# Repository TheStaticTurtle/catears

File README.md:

# Catears

High-tech, RGB LED-matrix cat ears, built for fun.

Each ear and each side of the headband carries a small 2D matrix of tiny XL-1010 WS2812B LEDs, driven by an ESP32-S3 running [WLED](https://kno.wled.ge/) with sound-reactive animations, all powered over a single USB-C cable.

## Revisions

| Version | Description |
|---------|-------------|
| V1 / V2 | The original 3D-printed ears and the single-color "Light-Up" variant from the C3CAT assembly (not mine, just the inspiration). |
| V3 | Full-band 5mm addressable COB RGB strip, custom 3D-printed frame, TinyPICO ESP32 and battery in a bulky box. |
| V4.1 | Ear-shaped LED matrix test board to validate the LEDs, power and WLED. |
| V4.2 | ESP32-S3 on the PCB, USB-PD and a buck converter per panel. Over-engineered: it overheated and WiFi was poor (2-layer, then 4-layer respin, then a bypassed DC-DC for 39C3). |
| V4.3 | Current version. Plain 5V in, MPM3805 for 3.3V, tuned WiFi antenna, grid-aligned LEDs, SLS-printed PA12 frame, silicone-mounted PCBs. |

## Repository layout

- `cad/`: 3D models of the headband and ears
- `electronics/`: KiCad projects for each PCB revision
- `wled/`: WLED config, presets and the 2D LED map (generated from the KiCad netlist by `gen_ledmap.py`)

## Read more

The full story, with the mistakes, photos and lessons learned, is in the article:
**[Building high-tech catears for fun and definitively not profit](https://blog.thestaticturtle.fr/building-high-tech-catears-for-fun-and-definitely-not-profit)**

## License

See [LICENSE.md](LICENSE.md).

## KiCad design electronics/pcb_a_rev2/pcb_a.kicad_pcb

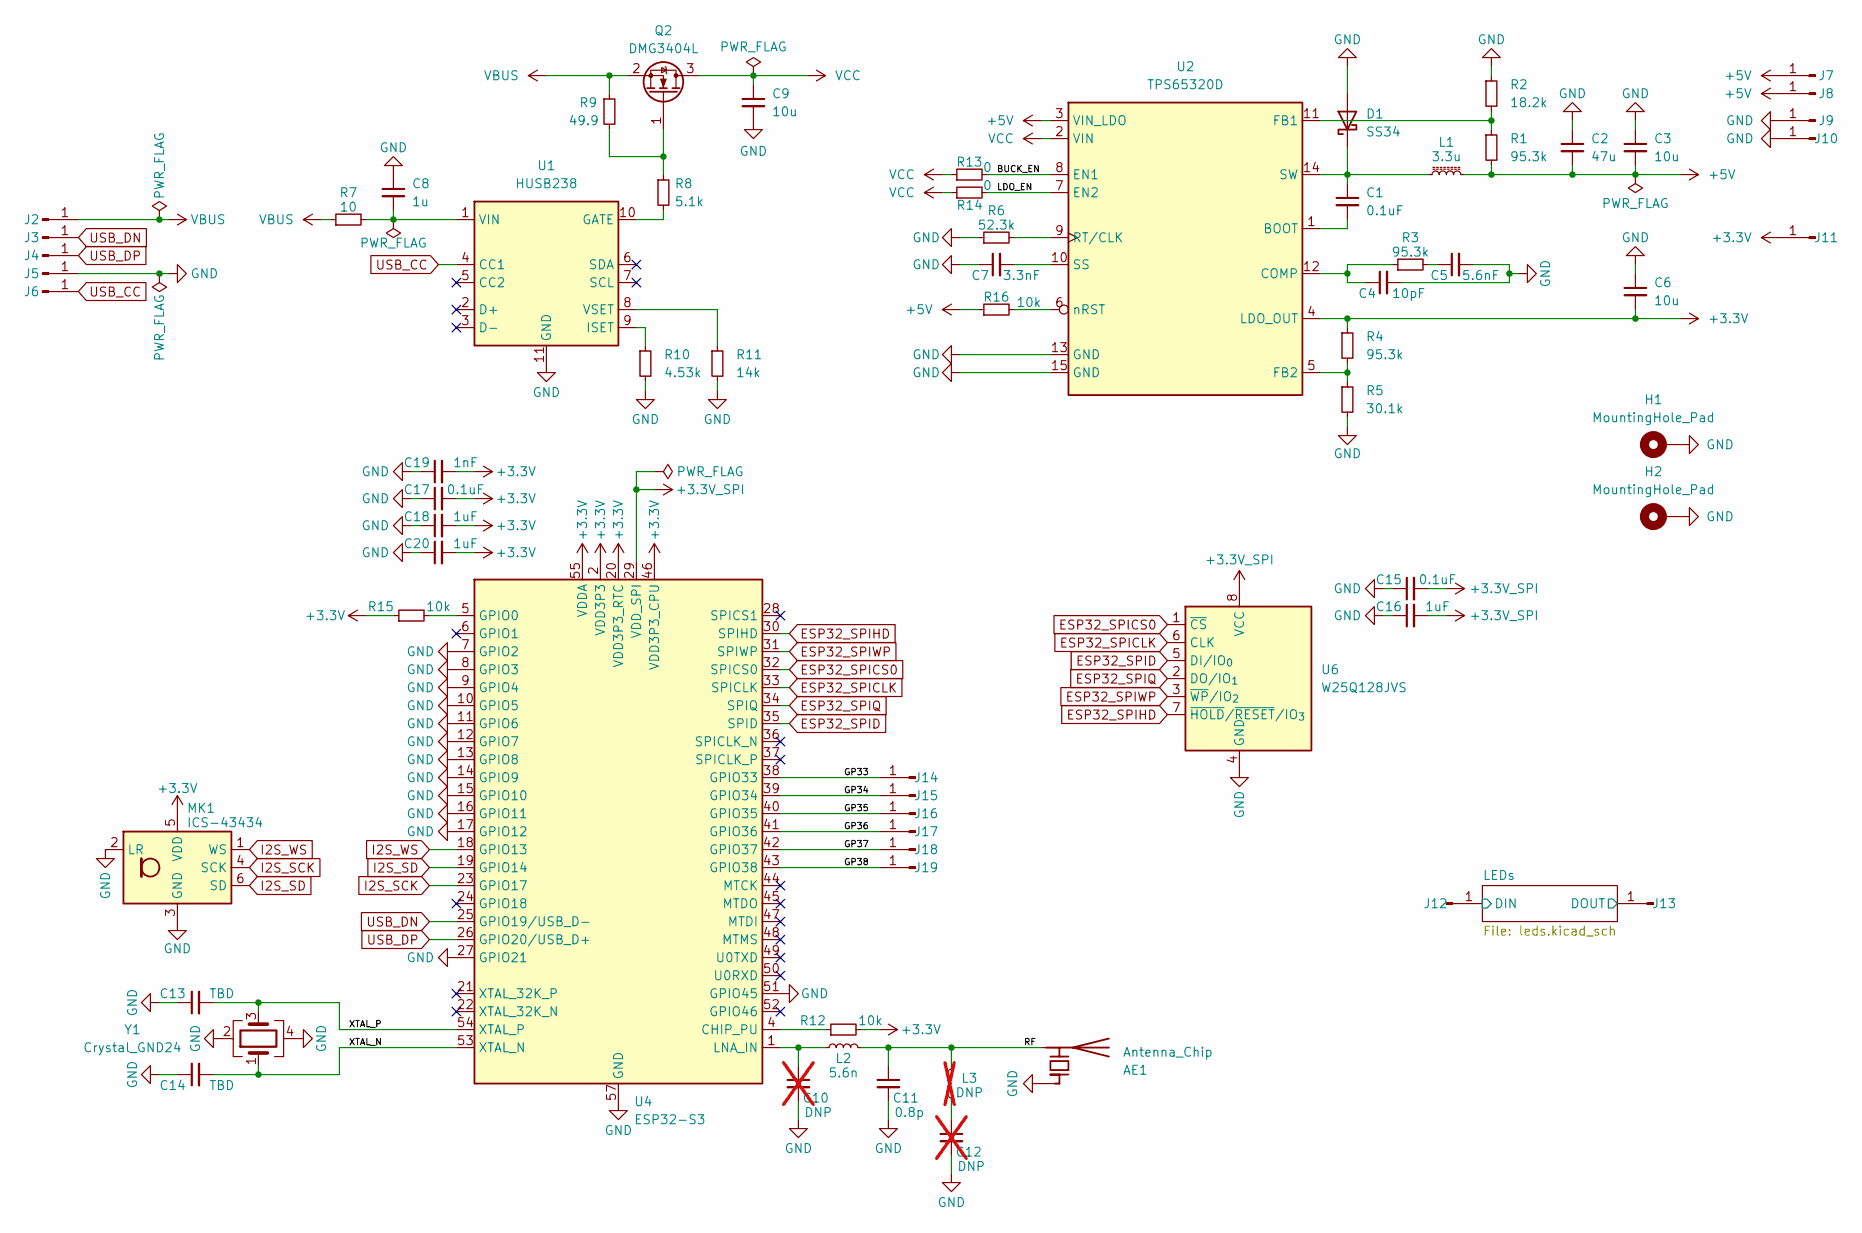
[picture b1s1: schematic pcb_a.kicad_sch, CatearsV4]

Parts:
AE1: Antenna_Chip; Johanson_2450AT43F0100
C1, C15, C17: 0.1uF; C_0603_1608Metric
C2: 47u; C_0603_1608Metric
C3, C6, C9: 10u; C_0603_1608Metric
C4: 10pF; C_0603_1608Metric
C5: 5.6nF; C_0603_1608Metric
C7: 3.3nF; C_0603_1608Metric
C8: 1u; C_0603_1608Metric
C10, C12: DNP; C_0603_1608Metric; not fitted
C11: 0.8p; C_0603_1608Metric
C13, C14: TBD; C_0603_1608Metric
C16, C18, C20: 1uF; C_0603_1608Metric
C19: 1nF; C_0603_1608Metric
D1: SS34; D_SMA
H1: MountingHole_Pad; 7466302R_thin
H2: MountingHole_Pad; 7466302R_thin_halved
J2, J3, J4, J5, J6, J7, J8, J9, J10, J11, J12, J13, J14, J15, J16, J17, J18, J19: Conn_01x01_Pin; TestPoint_Pad_1.5x1.5mm
L1: 3.3u; L_Wurth_WE-LQSH-4020
L2: 5.6n; L_0603_1608Metric
L3: DNP; L_0603_1608Metric; not fitted
MK1: ICS-43434; InvenSense_ICS-43434-6_3.5x2.65mm
Q2: DMG3404L; SOT-23
R1, R3, R4: 95.3k; R_0603_1608Metric
R2: 18.2k; R_0603_1608Metric
R5: 30.1k; R_0603_1608Metric
R6: 52.3k; R_0603_1608Metric
R7: 10; R_0603_1608Metric
R8: 5.1k; R_0603_1608Metric
R9: 49.9; R_0603_1608Metric
R10: 4.53k; R_0603_1608Metric
R11: 14k; R_0603_1608Metric
R12, R15, R16: 10k; R_0603_1608Metric
R13, R14: 0; R_0603_1608Metric
U1: HUSB238; DFN-10-1EP_3x3mm_P0.5mm_EP1.58x2.35mm
U2: TPS65320D; HTSSOP-14-1EP_4.4x5mm_P0.65mm_EP3.4x5mm_Mask3x3.1mm
U4: ESP32-S3; QFN-56-1EP_7x7mm_P0.4mm_EP4x4mm
U6: W25Q128JVS; SOIC-8_5.3x5.3mm_P1.27mm
Y1: Crystal_GND24; Crystal_SMD_5032-4Pin_5.0x3.2mm

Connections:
+3.3V: C6.2, C17.2, C18.2, C19.2, C20.2, J11.1, MK1.5 (VDD), R4.1, R12.2, R15.1, U2.4 (LDO_OUT), U4.2 (VDD3P3), U4.3 (VDD3P3), U4.20 (VDD3P3_RTC), U4.46 (VDD3P3_CPU), U4.55 (VDDA), U4.56 (VDDA)
+3.3V_SPI: C15.2, C16.2, U4.29 (VDD_SPI), U6.8 (VCC)
+5V: C2.2, C3.2, J7.1, J8.1, L1.2, R1.2, R16.1, U2.3 (VIN_LDO); also elsewhere on the board
/BUCK_EN: R13.2, U2.8 (EN1)
/GP33: J14.1, U4.38 (GPIO33)
/GP34: J15.1, U4.39 (GPIO34)
/GP35: J16.1, U4.40 (GPIO35)
/GP36: J17.1, U4.41 (GPIO36)
/GP37: J18.1, U4.42 (GPIO37)
/GP38: J19.1, U4.43 (GPIO38)
/LDO_EN: R14.2, U2.7 (EN2)
/LEDs/DIN: J12.1; also elsewhere on the board
/LEDs/DOUT: J13.1; also elsewhere on the board
/RF: AE1.2 (PCB_Trace), C11.1, L2.2, L3.2
/XTAL_N: C14.2, U4.53 (XTAL_N), Y1.1
/XTAL_P: C13.2, U4.54 (XTAL_P), Y1.3
ESP32_SPICLK: U4.33 (SPICLK), U6.6 (CLK)
ESP32_SPICS0: U4.32 (SPICS0), U6.1 (~CS)
ESP32_SPID: U4.35 (SPID), U6.5 (DI/IO_{0})
ESP32_SPIHD: U4.30 (SPIHD), U6.7 (~HOLD/~RESET/IO_{3})
ESP32_SPIQ: U4.34 (SPIQ), U6.2 (DO/IO_{1})
ESP32_SPIWP: U4.31 (SPIWP), U6.3 (~WP/IO_{2})
GND: AE1.1 (FEED), C2.1, C3.1, C4.2, C5.2, C6.1, C7.1, C8.1, C9.2, C10.2, C11.2, C12.2, C13.1, C14.1, C15.1, C16.1, C17.1, C18.1, C19.1, C20.1, D1.2 (A), H1.1, H2.1, J5.1, J9.1, J10.1, MK1.2 (LR), MK1.3 (GND), R2.1, R5.2, R6.1, R10.2, R11.2, U1.11 (GND), U2.13 (GND), U2.15 (GND), U4.7 (GPIO2), U4.8 (GPIO3), U4.9 (GPIO4), U4.10 (GPIO5), U4.11 (GPIO6), U4.12 (GPIO7), U4.13 (GPIO8), U4.14 (GPIO9), U4.15 (GPIO10), U4.16 (GPIO11), U4.17 (GPIO12), U4.27 (GPIO21), U4.51 (GPIO45), U4.57 (GND), U6.4 (GND), Y1.2, Y1.4; also elsewhere on the board
I2S_SCK: MK1.4 (SCK), U4.23 (GPIO17)
I2S_SD: MK1.6 (SD), U4.19 (GPIO14)
I2S_WS: MK1.1 (WS), U4.18 (GPIO13)
unnamed: C5.1, R3.2
unnamed: C12.1, L3.1
unnamed: C1.1, D1.1 (K), L1.1, U2.14 (SW)
unnamed: Q2.1 (G), R8.1, R9.2
unnamed: R8.2, U1.10 (GATE)
unnamed: R10.1, U1.9 (ISET)
unnamed: C8.2, R7.2, U1.1 (VIN)
unnamed: R11.1, U1.8 (VSET)
unnamed: C1.2, U2.1 (BOOT)
unnamed: C4.1, R3.1, U2.12 (COMP)
unnamed: R1.1, R2.2, U2.11 (FB1)
unnamed: R4.2, R5.1, U2.5 (FB2)
unnamed: R6.2, U2.9 (RT/CLK)
unnamed: C7.2, U2.10 (SS)
unnamed: R16.2, U2.6 (nRST)
unnamed: R12.1, U4.4 (CHIP_PU)
unnamed: R15.2, U4.5 (GPIO0)
unnamed: C10.1, L2.1, U4.1 (LNA_IN)
USB_CC: J6.1, U1.4 (CC1)
USB_DN: J3.1, U4.25 (GPIO19/USB_D-)
USB_DP: J4.1, U4.26 (GPIO20/USB_D+)
VBUS: J2.1, Q2.2 (S), R7.1, R9.1
VCC: C9.1, Q2.3 (D), R13.1, R14.1, U2.2 (VIN)

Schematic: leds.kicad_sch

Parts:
D2, D3, D4, D5, D6, D7, D8, D9, D10, D11, D12, D13, D14, D15, D16, D17, D18, D19, D20, D21, D22, D23, D24, D25, D26, D27, D28, D29, D30, D31, D32, D33, D34, D35, D36, D37, D38, D39, D40, D41, D42, D43, D44, D45, D46, D47, D48, D49, D50, D51, D52, D53, D54, D55, D56, D57, D58, D59, D60, D61, D62, D63, D64, D65, D66, D67, D68, D69, D70, D71, D72, D73, D74, D75, D76, D77, D78, D79, D80, D81, D82, D83, D84, D85, D86, D87, D88, D89, D90, D91, D92, D93, D94, D95, D96, D97, D98, D99, D100, D101, D102, D103, D104, D105, D106, D107, D108, D109, D110, D111, D112, D113, D114, D115, D116, D117, D118, D119, D120, D121, D122, D123, D124, D125, D126, D127, D128, D129, D130, D131, D132, D133, D134, D135, D136, D137, D138, D139, D140, D141, D142, D143, D144, D145, D146, D147, D148, D149, D150, D151, D152, D153, D154, D155, D156, D157, D158, D159, D160, D161, D162, D163, D164, D165, D166, D167, D168, D169, D170, D171, D172, D173, D174, D175, D176, D177, D178, D179, D180, D181, D182, D183, D184, D185, D186, D187, D188, D189, D190, D191, D192, D193, D194, D195, D196, D197, D198, D199, D200, D201, D202, D203, D204, D205, D206, D207, D208, D209, D210, D211, D212, D213, D214, D215, D216, D217, D218, D219, D220, D221, D222, D223, D224, D225, D226, D227, D228, D229, D230, D231, D232, D233, D234, D235, D236, D237, D238, D239, D240, D241, D242, D243, D244, D245, D246, D247, D248, D249, D250, D251, D252, D253, D254, D255, D257, D258, D259, D260, D261, D262, D263, D264, D265, D266, D267, D268, D269, D270, D271, D272, D273, D274, D275, D276, D277, D278, D279, D280, D281, D282, D283, D284, D285, D286, D287, D288, D289, D290, D291, D292, D293, D294, D295, D296, D297, D298, D299, D300, D301, D302, D303, D304, D305, D306, D307, D308, D309, D310, D311, D312, D313, D314, D315, D316, D317, D318, D319, D320, D321, D322, D323, D324, D325, D326, D327, D328: XL-1010; XL-1010RGBC

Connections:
+5V: D2.2 (VDD), D3.2 (VDD), D4.2 (VDD), D5.2 (VDD), D6.2 (VDD), D7.2 (VDD), D8.2 (VDD), D9.2 (VDD), D10.2 (VDD), D11.2 (VDD), D12.2 (VDD), D13.2 (VDD), D14.2 (VDD), D15.2 (VDD), D16.2 (VDD), D17.2 (VDD), D18.2 (VDD), D19.2 (VDD), D20.2 (VDD), D21.2 (VDD), D22.2 (VDD), D23.2 (VDD), D24.2 (VDD), D25.2 (VDD), D26.2 (VDD), D27.2 (VDD), D28.2 (VDD), D29.2 (VDD), D30.2 (VDD), D31.2 (VDD), D32.2 (VDD), D33.2 (VDD), D34.2 (VDD), D35.2 (VDD), D36.2 (VDD), D37.2 (VDD), D38.2 (VDD), D39.2 (VDD), D40.2 (VDD), D41.2 (VDD), D42.2 (VDD), D43.2 (VDD), D44.2 (VDD), D45.2 (VDD), D46.2 (VDD), D47.2 (VDD), D48.2 (VDD), D49.2 (VDD), D50.2 (VDD), D51.2 (VDD), D52.2 (VDD), D53.2 (VDD), D54.2 (VDD), D55.2 (VDD), D56.2 (VDD), D57.2 (VDD), D58.2 (VDD), D59.2 (VDD), D60.2 (VDD), D61.2 (VDD), D62.2 (VDD), D63.2 (VDD), D64.2 (VDD), D65.2 (VDD), D66.2 (VDD), D67.2 (VDD), D68.2 (VDD), D69.2 (VDD), D70.2 (VDD), D71.2 (VDD), D72.2 (VDD), D73.2 (VDD), D74.2 (VDD), D75.2 (VDD), D76.2 (VDD), D77.2 (VDD), D78.2 (VDD), D79.2 (VDD), D80.2 (VDD), D81.2 (VDD), D82.2 (VDD), D83.2 (VDD), D84.2 (VDD), D85.2 (VDD), D86.2 (VDD), D87.2 (VDD), D88.2 (VDD), D89.2 (VDD), D90.2 (VDD), D91.2 (VDD), D92.2 (VDD), D93.2 (VDD), D94.2 (VDD), D95.2 (VDD), D96.2 (VDD), D97.2 (VDD), D98.2 (VDD), D99.2 (VDD), D100.2 (VDD), D101.2 (VDD), D102.2 (VDD), D103.2 (VDD), D104.2 (VDD), D105.2 (VDD), D106.2 (VDD), D107.2 (VDD), D108.2 (VDD), D109.2 (VDD), D110.2 (VDD), D111.2 (VDD), D112.2 (VDD), D113.2 (VDD), D114.2 (VDD), D115.2 (VDD), D116.2 (VDD), D117.2 (VDD), D118.2 (VDD), D119.2 (VDD), D120.2 (VDD), D121.2 (VDD), D122.2 (VDD), D123.2 (VDD), D124.2 (VDD), D125.2 (VDD), D126.2 (VDD), D127.2 (VDD), D128.2 (VDD), D129.2 (VDD), D130.2 (VDD), D131.2 (VDD), D132.2 (VDD), D133.2 (VDD), D134.2 (VDD), D135.2 (VDD), D136.2 (VDD), D137.2 (VDD), D138.2 (VDD), D139.2 (VDD), D140.2 (VDD), D141.2 (VDD), D142.2 (VDD), D143.2 (VDD), D144.2 (VDD), D145.2 (VDD), D146.2 (VDD), D147.2 (VDD), D148.2 (VDD), D149.2 (VDD), D150.2 (VDD), D151.2 (VDD), D152.2 (VDD), D153.2 (VDD), D154.2 (VDD), D155.2 (VDD), D156.2 (VDD), D157.2 (VDD), D158.2 (VDD), D159.2 (VDD), D160.2 (VDD), D161.2 (VDD), D162.2 (VDD), D163.2 (VDD), D164.2 (VDD), D165.2 (VDD), D166.2 (VDD), D167.2 (VDD), D168.2 (VDD), D169.2 (VDD), D170.2 (VDD), D171.2 (VDD), D172.2 (VDD), D173.2 (VDD), D174.2 (VDD), D175.2 (VDD), D176.2 (VDD), D177.2 (VDD), D178.2 (VDD), D179.2 (VDD), D180.2 (VDD), D181.2 (VDD), D182.2 (VDD), D183.2 (VDD), D184.2 (VDD), D185.2 (VDD), D186.2 (VDD), D187.2 (VDD), D188.2 (VDD), D189.2 (VDD), D190.2 (VDD), D191.2 (VDD), D192.2 (VDD), D193.2 (VDD), D194.2 (VDD), D195.2 (VDD), D196.2 (VDD), D197.2 (VDD), D198.2 (VDD), D199.2 (VDD), D200.2 (VDD), D201.2 (VDD), D202.2 (VDD), D203.2 (VDD), D204.2 (VDD), D205.2 (VDD), D206.2 (VDD), D207.2 (VDD), D208.2 (VDD), D209.2 (VDD), D210.2 (VDD), D211.2 (VDD), D212.2 (VDD), D213.2 (VDD), D214.2 (VDD), D215.2 (VDD), D216.2 (VDD), D217.2 (VDD), D218.2 (VDD), D219.2 (VDD), D220.2 (VDD), D221.2 (VDD), D222.2 (VDD), D223.2 (VDD), D224.2 (VDD), D225.2 (VDD), D226.2 (VDD), D227.2 (VDD), D228.2 (VDD), D229.2 (VDD), D230.2 (VDD), D231.2 (VDD), D232.2 (VDD), D233.2 (VDD), D234.2 (VDD), D235.2 (VDD), D236.2 (VDD), D237.2 (VDD), D238.2 (VDD), D239.2 (VDD), D240.2 (VDD), D241.2 (VDD), D242.2 (VDD), D243.2 (VDD), D244.2 (VDD), D245.2 (VDD), D246.2 (VDD), D247.2 (VDD), D248.2 (VDD), D249.2 (VDD), D250.2 (VDD), D251.2 (VDD), D252.2 (VDD), D253.2 (VDD), D254.2 (VDD), D255.2 (VDD), D257.2 (VDD), D258.2 (VDD), D259.2 (VDD), D260.2 (VDD), D261.2 (VDD), D262.2 (VDD), D263.2 (VDD), D264.2 (VDD), D265.2 (VDD), D266.2 (VDD), D267.2 (VDD), D268.2 (VDD), D269.2 (VDD), D270.2 (VDD), D271.2 (VDD), D272.2 (VDD), D273.2 (VDD), D274.2 (VDD), D275.2 (VDD), D276.2 (VDD), D277.2 (VDD), D278.2 (VDD), D279.2 (VDD), D280.2 (VDD), D281.2 (VDD), D282.2 (VDD), D283.2 (VDD), D284.2 (VDD), D285.2 (VDD), D286.2 (VDD), D287.2 (VDD), D288.2 (VDD), D289.2 (VDD), D290.2 (VDD), D291.2 (VDD), D292.2 (VDD), D293.2 (VDD), D294.2 (VDD), D295.2 (VDD), D296.2 (VDD), D297.2 (VDD), D298.2 (VDD), D299.2 (VDD), D300.2 (VDD), D301.2 (VDD), D302.2 (VDD), D303.2 (VDD), D304.2 (VDD), D305.2 (VDD), D306.2 (VDD), D307.2 (VDD), D308.2 (VDD), D309.2 (VDD), D310.2 (VDD), D311.2 (VDD), D312.2 (VDD), D313.2 (VDD), D314.2 (VDD), D315.2 (VDD), D316.2 (VDD), D317.2 (VDD), D318.2 (VDD), D319.2 (VDD), D320.2 (VDD), D321.2 (VDD), D322.2 (VDD), D323.2 (VDD), D324.2 (VDD), D325.2 (VDD), D326.2 (VDD), D327.2 (VDD), D328.2 (VDD); also elsewhere on the board
/LEDs/DIN: D2.4 (DIN); also elsewhere on the board
/LEDs/DOUT: D328.1 (DOUT); also elsewhere on the board
GND: D2.3 (VSS), D3.3 (VSS), D4.3 (VSS), D5.3 (VSS), D6.3 (VSS), D7.3 (VSS), D8.3 (VSS), D9.3 (VSS), D10.3 (VSS), D11.3 (VSS), D12.3 (VSS), D13.3 (VSS), D14.3 (VSS), D15.3 (VSS), D16.3 (VSS), D17.3 (VSS), D18.3 (VSS), D19.3 (VSS), D20.3 (VSS), D21.3 (VSS), D22.3 (VSS), D23.3 (VSS), D24.3 (VSS), D25.3 (VSS), D26.3 (VSS), D27.3 (VSS), D28.3 (VSS), D29.3 (VSS), D30.3 (VSS), D31.3 (VSS), D32.3 (VSS), D33.3 (VSS), D34.3 (VSS), D35.3 (VSS), D36.3 (VSS), D37.3 (VSS), D38.3 (VSS), D39.3 (VSS), D40.3 (VSS), D41.3 (VSS), D42.3 (VSS), D43.3 (VSS), D44.3 (VSS), D45.3 (VSS), D46.3 (VSS), D47.3 (VSS), D48.3 (VSS), D49.3 (VSS), D50.3 (VSS), D51.3 (VSS), D52.3 (VSS), D53.3 (VSS), D54.3 (VSS), D55.3 (VSS), D56.3 (VSS), D57.3 (VSS), D58.3 (VSS), D59.3 (VSS), D60.3 (VSS), D61.3 (VSS), D62.3 (VSS), D63.3 (VSS), D64.3 (VSS), D65.3 (VSS), D66.3 (VSS), D67.3 (VSS), D68.3 (VSS), D69.3 (VSS), D70.3 (VSS), D71.3 (VSS), D72.3 (VSS), D73.3 (VSS), D74.3 (VSS), D75.3 (VSS), D76.3 (VSS), D77.3 (VSS), D78.3 (VSS), D79.3 (VSS), D80.3 (VSS), D81.3 (VSS), D82.3 (VSS), D83.3 (VSS), D84.3 (VSS), D85.3 (VSS), D86.3 (VSS), D87.3 (VSS), D88.3 (VSS), D89.3 (VSS), D90.3 (VSS), D91.3 (VSS), D92.3 (VSS), D93.3 (VSS), D94.3 (VSS), D95.3 (VSS), D96.3 (VSS), D97.3 (VSS), D98.3 (VSS), D99.3 (VSS), D100.3 (VSS), D101.3 (VSS), D102.3 (VSS), D103.3 (VSS), D104.3 (VSS), D105.3 (VSS), D106.3 (VSS), D107.3 (VSS), D108.3 (VSS), D109.3 (VSS), D110.3 (VSS), D111.3 (VSS), D112.3 (VSS), D113.3 (VSS), D114.3 (VSS), D115.3 (VSS), D116.3 (VSS), D117.3 (VSS), D118.3 (VSS), D119.3 (VSS), D120.3 (VSS), D121.3 (VSS), D122.3 (VSS), D123.3 (VSS), D124.3 (VSS), D125.3 (VSS), D126.3 (VSS), D127.3 (VSS), D128.3 (VSS), D129.3 (VSS), D130.3 (VSS), D131.3 (VSS), D132.3 (VSS), D133.3 (VSS), D134.3 (VSS), D135.3 (VSS), D136.3 (VSS), D137.3 (VSS), D138.3 (VSS), D139.3 (VSS), D140.3 (VSS), D141.3 (VSS), D142.3 (VSS), D143.3 (VSS), D144.3 (VSS), D145.3 (VSS), D146.3 (VSS), D147.3 (VSS), D148.3 (VSS), D149.3 (VSS), D150.3 (VSS), D151.3 (VSS), D152.3 (VSS), D153.3 (VSS), D154.3 (VSS), D155.3 (VSS), D156.3 (VSS), D157.3 (VSS), D158.3 (VSS), D159.3 (VSS), D160.3 (VSS), D161.3 (VSS), D162.3 (VSS), D163.3 (VSS), D164.3 (VSS), D165.3 (VSS), D166.3 (VSS), D167.3 (VSS), D168.3 (VSS), D169.3 (VSS), D170.3 (VSS), D171.3 (VSS), D172.3 (VSS), D173.3 (VSS), D174.3 (VSS), D175.3 (VSS), D176.3 (VSS), D177.3 (VSS), D178.3 (VSS), D179.3 (VSS), D180.3 (VSS), D181.3 (VSS), D182.3 (VSS), D183.3 (VSS), D184.3 (VSS), D185.3 (VSS), D186.3 (VSS), D187.3 (VSS), D188.3 (VSS), D189.3 (VSS), D190.3 (VSS), D191.3 (VSS), D192.3 (VSS), D193.3 (VSS), D194.3 (VSS), D195.3 (VSS), D196.3 (VSS), D197.3 (VSS), D198.3 (VSS), D199.3 (VSS), D200.3 (VSS), D201.3 (VSS), D202.3 (VSS), D203.3 (VSS), D204.3 (VSS), D205.3 (VSS), D206.3 (VSS), D207.3 (VSS), D208.3 (VSS), D209.3 (VSS), D210.3 (VSS), D211.3 (VSS), D212.3 (VSS), D213.3 (VSS), D214.3 (VSS), D215.3 (VSS), D216.3 (VSS), D217.3 (VSS), D218.3 (VSS), D219.3 (VSS), D220.3 (VSS), D221.3 (VSS), D222.3 (VSS), D223.3 (VSS), D224.3 (VSS), D225.3 (VSS), D226.3 (VSS), D227.3 (VSS), D228.3 (VSS), D229.3 (VSS), D230.3 (VSS), D231.3 (VSS), D232.3 (VSS), D233.3 (VSS), D234.3 (VSS), D235.3 (VSS), D236.3 (VSS), D237.3 (VSS), D238.3 (VSS), D239.3 (VSS), D240.3 (VSS), D241.3 (VSS), D242.3 (VSS), D243.3 (VSS), D244.3 (VSS), D245.3 (VSS), D246.3 (VSS), D247.3 (VSS), D248.3 (VSS), D249.3 (VSS), D250.3 (VSS), D251.3 (VSS), D252.3 (VSS), D253.3 (VSS), D254.3 (VSS), D255.3 (VSS), D257.3 (VSS), D258.3 (VSS), D259.3 (VSS), D260.3 (VSS), D261.3 (VSS), D262.3 (VSS), D263.3 (VSS), D264.3 (VSS), D265.3 (VSS), D266.3 (VSS), D267.3 (VSS), D268.3 (VSS), D269.3 (VSS), D270.3 (VSS), D271.3 (VSS), D272.3 (VSS), D273.3 (VSS), D274.3 (VSS), D275.3 (VSS), D276.3 (VSS), D277.3 (VSS), D278.3 (VSS), D279.3 (VSS), D280.3 (VSS), D281.3 (VSS), D282.3 (VSS), D283.3 (VSS), D284.3 (VSS), D285.3 (VSS), D286.3 (VSS), D287.3 (VSS), D288.3 (VSS), D289.3 (VSS), D290.3 (VSS), D291.3 (VSS), D292.3 (VSS), D293.3 (VSS), D294.3 (VSS), D295.3 (VSS), D296.3 (VSS), D297.3 (VSS), D298.3 (VSS), D299.3 (VSS), D300.3 (VSS), D301.3 (VSS), D302.3 (VSS), D303.3 (VSS), D304.3 (VSS), D305.3 (VSS), D306.3 (VSS), D307.3 (VSS), D308.3 (VSS), D309.3 (VSS), D310.3 (VSS), D311.3 (VSS), D312.3 (VSS), D313.3 (VSS), D314.3 (VSS), D315.3 (VSS), D316.3 (VSS), D317.3 (VSS), D318.3 (VSS), D319.3 (VSS), D320.3 (VSS), D321.3 (VSS), D322.3 (VSS), D323.3 (VSS), D324.3 (VSS), D325.3 (VSS), D326.3 (VSS), D327.3 (VSS), D328.3 (VSS); also elsewhere on the board
unnamed: D2.1 (DOUT), D3.4 (DIN)
unnamed: D3.1 (DOUT), D4.4 (DIN)
unnamed: D4.1 (DOUT), D5.4 (DIN)
unnamed: D5.1 (DOUT), D6.4 (DIN)
unnamed: D6.1 (DOUT), D7.4 (DIN)
unnamed: D7.1 (DOUT), D8.4 (DIN)
unnamed: D8.1 (DOUT), D9.4 (DIN)
unnamed: D9.1 (DOUT), D10.4 (DIN)
unnamed: D10.1 (DOUT), D11.4 (DIN)
unnamed: D11.1 (DOUT), D12.4 (DIN)
unnamed: D12.1 (DOUT), D13.4 (DIN)
unnamed: D13.1 (DOUT), D14.4 (DIN)
unnamed: D14.1 (DOUT), D15.4 (DIN)
unnamed: D15.1 (DOUT), D16.4 (DIN)
unnamed: D16.1 (DOUT), D17.4 (DIN)
unnamed: D17.1 (DOUT), D18.4 (DIN)
unnamed: D18.1 (DOUT), D19.4 (DIN)
unnamed: D19.1 (DOUT), D20.4 (DIN)
unnamed: D20.1 (DOUT), D21.4 (DIN)
unnamed: D21.1 (DOUT), D22.4 (DIN)
unnamed: D22.1 (DOUT), D23.4 (DIN)
unnamed: D23.1 (DOUT), D24.4 (DIN)
unnamed: D24.1 (DOUT), D25.4 (DIN)
unnamed: D25.1 (DOUT), D26.4 (DIN)
unnamed: D26.1 (DOUT), D27.4 (DIN)
unnamed: D27.1 (DOUT), D28.4 (DIN)
unnamed: D28.1 (DOUT), D29.4 (DIN)
unnamed: D29.1 (DOUT), D30.4 (DIN)
unnamed: D30.1 (DOUT), D31.4 (DIN)
unnamed: D31.1 (DOUT), D32.4 (DIN)
unnamed: D32.1 (DOUT), D33.4 (DIN)
unnamed: D33.1 (DOUT), D34.4 (DIN)
unnamed: D34.1 (DOUT), D35.4 (DIN)
unnamed: D35.1 (DOUT), D36.4 (DIN)
unnamed: D36.1 (DOUT), D37.4 (DIN)
unnamed: D37.1 (DOUT), D38.4 (DIN)
unnamed: D38.1 (DOUT), D39.4 (DIN)
unnamed: D39.1 (DOUT), D40.4 (DIN)
unnamed: D40.1 (DOUT), D41.4 (DIN)
unnamed: D41.1 (DOUT), D42.4 (DIN)
unnamed: D42.1 (DOUT), D43.4 (DIN)
unnamed: D43.1 (DOUT), D44.4 (DIN)
unnamed: D44.1 (DOUT), D45.4 (DIN)
unnamed: D45.1 (DOUT), D46.4 (DIN)
unnamed: D46.1 (DOUT), D47.4 (DIN)
unnamed: D47.1 (DOUT), D48.4 (DIN)
unnamed: D48.1 (DOUT), D49.4 (DIN)
unnamed: D49.1 (DOUT), D50.4 (DIN)
unnamed: D50.1 (DOUT), D51.4 (DIN)
unnamed: D51.1 (DOUT), D52.4 (DIN)
unnamed: D52.1 (DOUT), D53.4 (DIN)
unnamed: D53.1 (DOUT), D54.4 (DIN)
unnamed: D54.1 (DOUT), D55.4 (DIN)
unnamed: D55.1 (DOUT), D56.4 (DIN)
unnamed: D56.1 (DOUT), D57.4 (DIN)
unnamed: D57.1 (DOUT), D58.4 (DIN)
unnamed: D58.1 (DOUT), D59.4 (DIN)
unnamed: D59.1 (DOUT), D60.4 (DIN)
unnamed: D60.1 (DOUT), D61.4 (DIN)
unnamed: D61.1 (DOUT), D62.4 (DIN)
unnamed: D62.1 (DOUT), D63.4 (DIN)
unnamed: D63.1 (DOUT), D64.4 (DIN)
unnamed: D64.1 (DOUT), D65.4 (DIN)
unnamed: D65.1 (DOUT), D66.4 (DIN)
unnamed: D66.1 (DOUT), D67.4 (DIN)
unnamed: D67.1 (DOUT), D68.4 (DIN)
unnamed: D68.1 (DOUT), D69.4 (DIN)
unnamed: D69.1 (DOUT), D70.4 (DIN)
unnamed: D70.1 (DOUT), D71.4 (DIN)
unnamed: D71.1 (DOUT), D72.4 (DIN)
unnamed: D72.1 (DOUT), D73.4 (DIN)
unnamed: D73.1 (DOUT), D74.4 (DIN)
unnamed: D74.1 (DOUT), D75.4 (DIN)
unnamed: D75.1 (DOUT), D76.4 (DIN)
unnamed: D76.1 (DOUT), D77.4 (DIN)
unnamed: D77.1 (DOUT), D78.4 (DIN)
unnamed: D78.1 (DOUT), D79.4 (DIN)
unnamed: D79.1 (DOUT), D80.4 (DIN)
unnamed: D80.1 (DOUT), D81.4 (DIN)
unnamed: D81.1 (DOUT), D82.4 (DIN)
unnamed: D82.1 (DOUT), D83.4 (DIN)
unnamed: D83.1 (DOUT), D84.4 (DIN)
unnamed: D84.1 (DOUT), D85.4 (DIN)
unnamed: D85.1 (DOUT), D86.4 (DIN)
unnamed: D86.1 (DOUT), D87.4 (DIN)
unnamed: D87.1 (DOUT), D88.4 (DIN)
unnamed: D88.1 (DOUT), D89.4 (DIN)
unnamed: D89.1 (DOUT), D90.4 (DIN)
unnamed: D90.1 (DOUT), D91.4 (DIN)
unnamed: D91.1 (DOUT), D92.4 (DIN)
unnamed: D92.1 (DOUT), D93.4 (DIN)
unnamed: D93.1 (DOUT), D94.4 (DIN)
unnamed: D94.1 (DOUT), D95.4 (DIN)
unnamed: D95.1 (DOUT), D96.4 (DIN)
unnamed: D96.1 (DOUT), D97.4 (DIN)
unnamed: D97.1 (DOUT), D98.4 (DIN)
unnamed: D98.1 (DOUT), D99.4 (DIN)
unnamed: D99.1 (DOUT), D100.4 (DIN)
unnamed: D100.1 (DOUT), D101.4 (DIN)
unnamed: D101.1 (DOUT), D102.4 (DIN)
unnamed: D102.1 (DOUT), D103.4 (DIN)
unnamed: D103.1 (DOUT), D104.4 (DIN)
unnamed: D104.1 (DOUT), D105.4 (DIN)
unnamed: D105.1 (DOUT), D106.4 (DIN)
unnamed: D106.1 (DOUT), D107.4 (DIN)
unnamed: D107.1 (DOUT), D108.4 (DIN)
unnamed: D108.1 (DOUT), D109.4 (DIN)
unnamed: D109.1 (DOUT), D110.4 (DIN)
unnamed: D110.1 (DOUT), D111.4 (DIN)
unnamed: D111.1 (DOUT), D112.4 (DIN)
unnamed: D112.1 (DOUT), D113.4 (DIN)
unnamed: D113.1 (DOUT), D114.4 (DIN)
unnamed: D114.1 (DOUT), D115.4 (DIN)
unnamed: D115.1 (DOUT), D116.4 (DIN)
unnamed: D116.1 (DOUT), D117.4 (DIN)
unnamed: D117.1 (DOUT), D118.4 (DIN)
unnamed: D118.1 (DOUT), D119.4 (DIN)
unnamed: D119.1 (DOUT), D120.4 (DIN)
unnamed: D120.1 (DOUT), D121.4 (DIN)
unnamed: D121.1 (DOUT), D122.4 (DIN)
unnamed: D122.1 (DOUT), D123.4 (DIN)
unnamed: D123.1 (DOUT), D124.4 (DIN)
unnamed: D124.1 (DOUT), D125.4 (DIN)
unnamed: D125.1 (DOUT), D126.4 (DIN)
unnamed: D126.1 (DOUT), D127.4 (DIN)
unnamed: D127.1 (DOUT), D128.4 (DIN)
unnamed: D128.1 (DOUT), D129.4 (DIN)
unnamed: D129.1 (DOUT), D130.4 (DIN)
unnamed: D130.1 (DOUT), D131.4 (DIN)
unnamed: D131.1 (DOUT), D132.4 (DIN)
unnamed: D132.1 (DOUT), D133.4 (DIN)
unnamed: D133.1 (DOUT), D134.4 (DIN)
unnamed: D134.1 (DOUT), D135.4 (DIN)
unnamed: D135.1 (DOUT), D136.4 (DIN)
unnamed: D136.1 (DOUT), D137.4 (DIN)
unnamed: D137.1 (DOUT), D138.4 (DIN)
unnamed: D138.1 (DOUT), D139.4 (DIN)
unnamed: D139.1 (DOUT), D140.4 (DIN)
unnamed: D140.1 (DOUT), D141.4 (DIN)
unnamed: D141.1 (DOUT), D142.4 (DIN)
unnamed: D142.1 (DOUT), D143.4 (DIN)
unnamed: D143.1 (DOUT), D144.4 (DIN)
unnamed: D144.1 (DOUT), D145.4 (DIN)
unnamed: D145.1 (DOUT), D146.4 (DIN)
unnamed: D146.1 (DOUT), D147.4 (DIN)
unnamed: D147.1 (DOUT), D148.4 (DIN)
unnamed: D148.1 (DOUT), D149.4 (DIN)
unnamed: D149.1 (DOUT), D150.4 (DIN)
unnamed: D150.1 (DOUT), D151.4 (DIN)
unnamed: D151.1 (DOUT), D152.4 (DIN)
unnamed: D152.1 (DOUT), D153.4 (DIN)
unnamed: D153.1 (DOUT), D154.4 (DIN)
unnamed: D154.1 (DOUT), D155.4 (DIN)
unnamed: D155.1 (DOUT), D156.4 (DIN)
unnamed: D156.1 (DOUT), D157.4 (DIN)
unnamed: D157.1 (DOUT), D158.4 (DIN)
unnamed: D158.1 (DOUT), D159.4 (DIN)
unnamed: D159.1 (DOUT), D160.4 (DIN)
unnamed: D160.1 (DOUT), D161.4 (DIN)
unnamed: D161.1 (DOUT), D162.4 (DIN)
unnamed: D162.1 (DOUT), D163.4 (DIN)
unnamed: D163.1 (DOUT), D164.4 (DIN)
unnamed: D164.1 (DOUT), D165.4 (DIN)
unnamed: D165.1 (DOUT), D166.4 (DIN)
unnamed: D166.1 (DOUT), D167.4 (DIN)
unnamed: D167.1 (DOUT), D168.4 (DIN)
unnamed: D168.1 (DOUT), D169.4 (DIN)
unnamed: D169.1 (DOUT), D170.4 (DIN)
unnamed: D170.1 (DOUT), D171.4 (DIN)
unnamed: D171.1 (DOUT), D172.4 (DIN)
unnamed: D172.1 (DOUT), D173.4 (DIN)
unnamed: D173.1 (DOUT), D174.4 (DIN)
unnamed: D174.1 (DOUT), D175.4 (DIN)
unnamed: D175.1 (DOUT), D176.4 (DIN)
unnamed: D176.1 (DOUT), D177.4 (DIN)
unnamed: D177.1 (DOUT), D178.4 (DIN)
unnamed: D178.1 (DOUT), D179.4 (DIN)
unnamed: D179.1 (DOUT), D180.4 (DIN)
unnamed: D180.1 (DOUT), D181.4 (DIN)
unnamed: D181.1 (DOUT), D182.4 (DIN)
unnamed: D182.1 (DOUT), D183.4 (DIN)
unnamed: D183.1 (DOUT), D184.4 (DIN)
unnamed: D184.1 (DOUT), D185.4 (DIN)
unnamed: D185.1 (DOUT), D186.4 (DIN)
unnamed: D186.1 (DOUT), D187.4 (DIN)
unnamed: D187.1 (DOUT), D188.4 (DIN)
unnamed: D188.1 (DOUT), D189.4 (DIN)
unnamed: D189.1 (DOUT), D190.4 (DIN)
unnamed: D190.1 (DOUT), D191.4 (DIN)
unnamed: D191.1 (DOUT), D192.4 (DIN)
unnamed: D192.1 (DOUT), D193.4 (DIN)
unnamed: D193.1 (DOUT), D194.4 (DIN)
unnamed: D194.1 (DOUT), D195.4 (DIN)
unnamed: D195.1 (DOUT), D196.4 (DIN)
unnamed: D196.1 (DOUT), D197.4 (DIN)
unnamed: D197.1 (DOUT), D198.4 (DIN)
unnamed: D198.1 (DOUT), D199.4 (DIN)
unnamed: D199.1 (DOUT), D200.4 (DIN)
unnamed: D200.1 (DOUT), D201.4 (DIN)
unnamed: D201.1 (DOUT), D202.4 (DIN)
unnamed: D202.1 (DOUT), D203.4 (DIN)
unnamed: D203.1 (DOUT), D204.4 (DIN)
unnamed: D204.1 (DOUT), D205.4 (DIN)
unnamed: D205.1 (DOUT), D206.4 (DIN)
unnamed: D206.1 (DOUT), D207.4 (DIN)
unnamed: D207.1 (DOUT), D208.4 (DIN)
unnamed: D208.1 (DOUT), D209.4 (DIN)
unnamed: D209.1 (DOUT), D210.4 (DIN)
unnamed: D210.1 (DOUT), D211.4 (DIN)
unnamed: D211.1 (DOUT), D212.4 (DIN)
unnamed: D212.1 (DOUT), D213.4 (DIN)
unnamed: D213.1 (DOUT), D214.4 (DIN)
unnamed: D214.1 (DOUT), D215.4 (DIN)
unnamed: D215.1 (DOUT), D216.4 (DIN)
unnamed: D216.1 (DOUT), D217.4 (DIN)
unnamed: D217.1 (DOUT), D218.4 (DIN)
unnamed: D218.1 (DOUT), D219.4 (DIN)
unnamed: D219.1 (DOUT), D220.4 (DIN)
unnamed: D220.1 (DOUT), D221.4 (DIN)
unnamed: D221.1 (DOUT), D222.4 (DIN)
unnamed: D222.1 (DOUT), D223.4 (DIN)
unnamed: D223.1 (DOUT), D224.4 (DIN)
unnamed: D224.1 (DOUT), D225.4 (DIN)
unnamed: D225.1 (DOUT), D226.4 (DIN)
unnamed: D226.1 (DOUT), D227.4 (DIN)
unnamed: D227.1 (DOUT), D228.4 (DIN)
unnamed: D228.1 (DOUT), D229.4 (DIN)
unnamed: D229.1 (DOUT), D230.4 (DIN)
unnamed: D230.1 (DOUT), D231.4 (DIN)
unnamed: D231.1 (DOUT), D232.4 (DIN)
unnamed: D232.1 (DOUT), D233.4 (DIN)
unnamed: D233.1 (DOUT), D234.4 (DIN)
unnamed: D234.1 (DOUT), D235.4 (DIN)
unnamed: D235.1 (DOUT), D236.4 (DIN)
unnamed: D236.1 (DOUT), D237.4 (DIN)
unnamed: D237.1 (DOUT), D238.4 (DIN)
unnamed: D238.1 (DOUT), D239.4 (DIN)
unnamed: D239.1 (DOUT), D240.4 (DIN)
unnamed: D240.1 (DOUT), D241.4 (DIN)
unnamed: D241.1 (DOUT), D242.4 (DIN)
unnamed: D242.1 (DOUT), D243.4 (DIN)
unnamed: D243.1 (DOUT), D244.4 (DIN)
unnamed: D244.1 (DOUT), D245.4 (DIN)
unnamed: D245.1 (DOUT), D246.4 (DIN)
unnamed: D246.1 (DOUT), D247.4 (DIN)
unnamed: D247.1 (DOUT), D248.4 (DIN)
unnamed: D248.1 (DOUT), D249.4 (DIN)
unnamed: D249.1 (DOUT), D250.4 (DIN)
unnamed: D250.1 (DOUT), D251.4 (DIN)
unnamed: D251.1 (DOUT), D252.4 (DIN)
unnamed: D252.1 (DOUT), D253.4 (DIN)
unnamed: D253.1 (DOUT), D254.4 (DIN)
unnamed: D254.1 (DOUT), D255.4 (DIN)
unnamed: D255.1 (DOUT), D257.4 (DIN)
unnamed: D257.1 (DOUT), D258.4 (DIN)
unnamed: D258.1 (DOUT), D259.4 (DIN)
unnamed: D259.1 (DOUT), D260.4 (DIN)
unnamed: D260.1 (DOUT), D261.4 (DIN)
unnamed: D261.1 (DOUT), D262.4 (DIN)
unnamed: D262.1 (DOUT), D263.4 (DIN)
unnamed: D263.1 (DOUT), D264.4 (DIN)
unnamed: D264.1 (DOUT), D265.4 (DIN)
unnamed: D265.1 (DOUT), D266.4 (DIN)
unnamed: D266.1 (DOUT), D267.4 (DIN)
unnamed: D267.1 (DOUT), D268.4 (DIN)
unnamed: D268.1 (DOUT), D269.4 (DIN)
unnamed: D269.1 (DOUT), D270.4 (DIN)
unnamed: D270.1 (DOUT), D271.4 (DIN)
unnamed: D271.1 (DOUT), D272.4 (DIN)
unnamed: D272.1 (DOUT), D273.4 (DIN)
unnamed: D273.1 (DOUT), D274.4 (DIN)
unnamed: D274.1 (DOUT), D275.4 (DIN)
unnamed: D275.1 (DOUT), D276.4 (DIN)
unnamed: D276.1 (DOUT), D277.4 (DIN)
unnamed: D277.1 (DOUT), D278.4 (DIN)
unnamed: D278.1 (DOUT), D279.4 (DIN)
unnamed: D279.1 (DOUT), D280.4 (DIN)
unnamed: D280.1 (DOUT), D281.4 (DIN)
unnamed: D281.1 (DOUT), D282.4 (DIN)
unnamed: D282.1 (DOUT), D283.4 (DIN)
unnamed: D283.1 (DOUT), D284.4 (DIN)
unnamed: D284.1 (DOUT), D285.4 (DIN)
unnamed: D285.1 (DOUT), D286.4 (DIN)
unnamed: D286.1 (DOUT), D287.4 (DIN)
unnamed: D287.1 (DOUT), D288.4 (DIN)
unnamed: D288.1 (DOUT), D289.4 (DIN)
unnamed: D289.1 (DOUT), D290.4 (DIN)
unnamed: D290.1 (DOUT), D291.4 (DIN)
unnamed: D291.1 (DOUT), D292.4 (DIN)
unnamed: D292.1 (DOUT), D293.4 (DIN)
unnamed: D293.1 (DOUT), D294.4 (DIN)
unnamed: D294.1 (DOUT), D295.4 (DIN)
unnamed: D295.1 (DOUT), D296.4 (DIN)
unnamed: D296.1 (DOUT), D297.4 (DIN)
unnamed: D297.1 (DOUT), D298.4 (DIN)
unnamed: D298.1 (DOUT), D299.4 (DIN)
unnamed: D299.1 (DOUT), D300.4 (DIN)
unnamed: D300.1 (DOUT), D301.4 (DIN)
unnamed: D301.1 (DOUT), D302.4 (DIN)
unnamed: D302.1 (DOUT), D303.4 (DIN)
unnamed: D303.1 (DOUT), D304.4 (DIN)
unnamed: D304.1 (DOUT), D305.4 (DIN)
unnamed: D305.1 (DOUT), D306.4 (DIN)
unnamed: D306.1 (DOUT), D307.4 (DIN)
unnamed: D307.1 (DOUT), D308.4 (DIN)
unnamed: D308.1 (DOUT), D309.4 (DIN)
unnamed: D309.1 (DOUT), D310.4 (DIN)
unnamed: D310.1 (DOUT), D311.4 (DIN)
unnamed: D311.1 (DOUT), D312.4 (DIN)
unnamed: D312.1 (DOUT), D313.4 (DIN)
unnamed: D313.1 (DOUT), D314.4 (DIN)
unnamed: D314.1 (DOUT), D315.4 (DIN)
unnamed: D315.1 (DOUT), D316.4 (DIN)
unnamed: D316.1 (DOUT), D317.4 (DIN)
unnamed: D317.1 (DOUT), D318.4 (DIN)
unnamed: D318.1 (DOUT), D319.4 (DIN)
unnamed: D319.1 (DOUT), D320.4 (DIN)
unnamed: D320.1 (DOUT), D321.4 (DIN)
unnamed: D321.1 (DOUT), D322.4 (DIN)
unnamed: D322.1 (DOUT), D323.4 (DIN)
unnamed: D323.1 (DOUT), D324.4 (DIN)
unnamed: D324.1 (DOUT), D325.4 (DIN)
unnamed: D325.1 (DOUT), D326.4 (DIN)
unnamed: D326.1 (DOUT), D327.4 (DIN)
unnamed: D327.1 (DOUT), D328.4 (DIN)

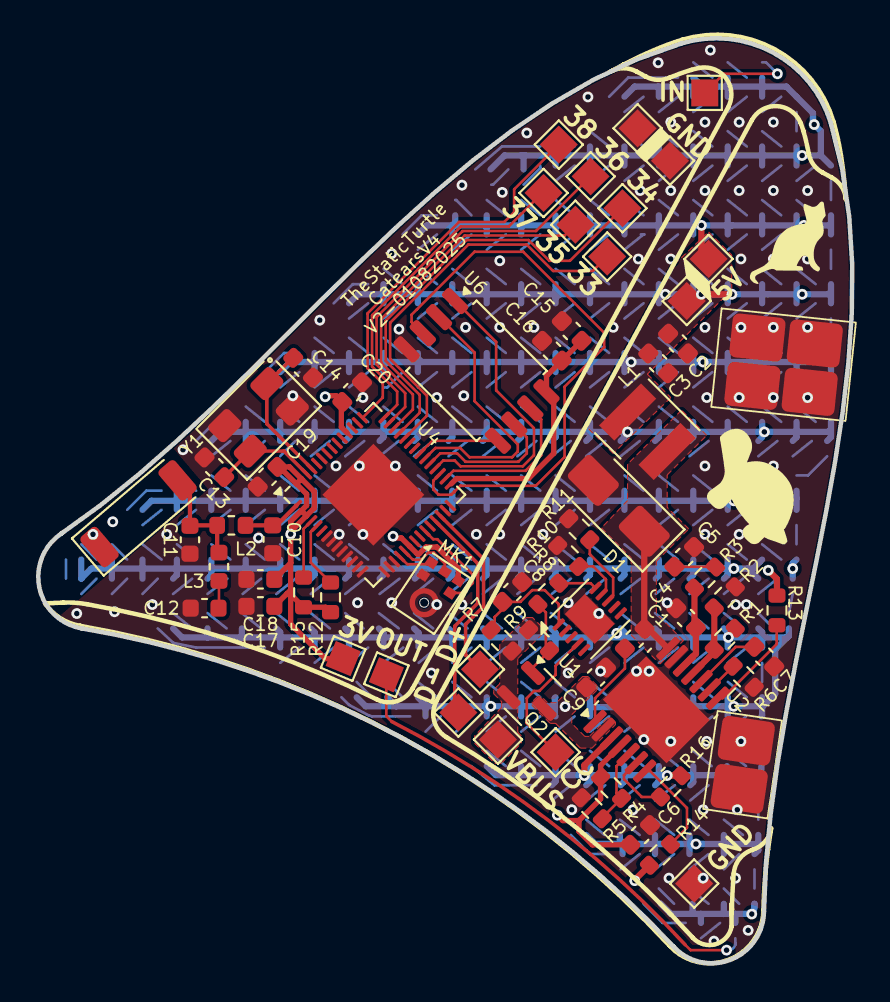
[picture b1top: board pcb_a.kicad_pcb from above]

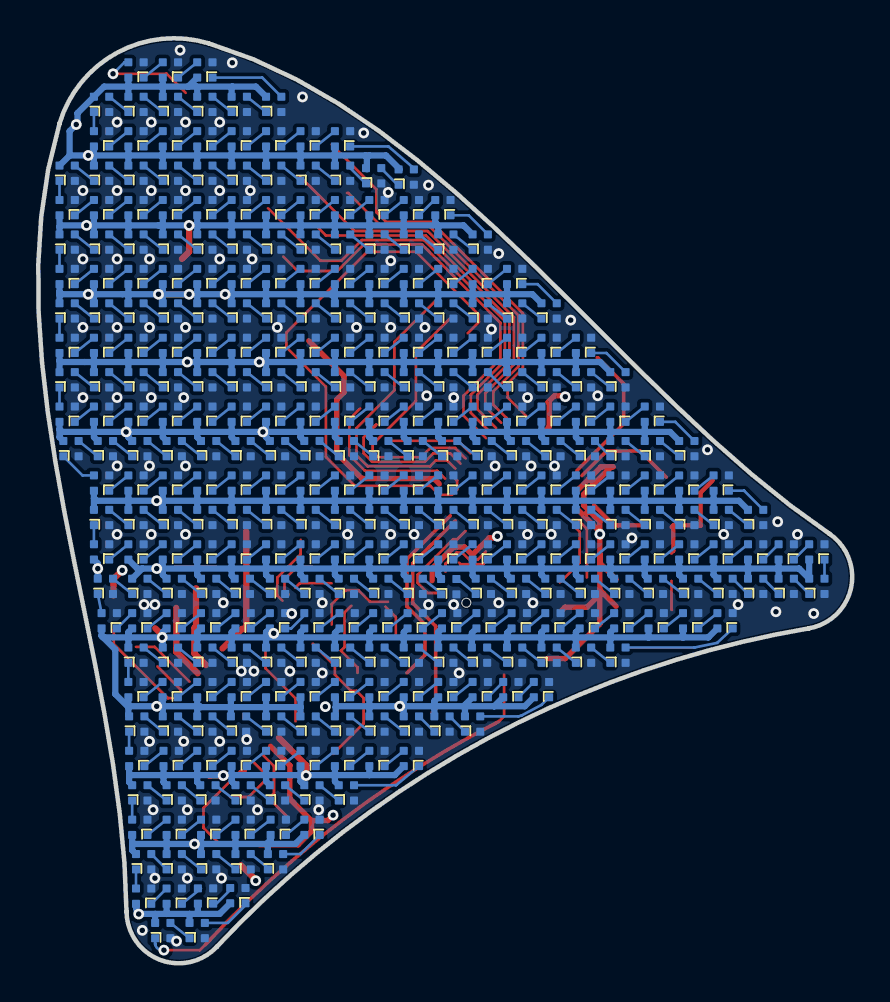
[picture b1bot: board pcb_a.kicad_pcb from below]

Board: 4 copper layers, 45.2 x 51.4 mm, 394 parts (326 on the bottom side), 374 nets.
